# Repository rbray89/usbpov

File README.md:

# usbpov

A small USB configurable POV toy

Some portions of this project are under the GNU General Public License (USB Device Driver Code for Atmel Devices) and should be distributed as-such. The licensing information can be found in /usbPOV-src/usbdrv

The remainder of the project is under the following license:

The MIT License (MIT)

Copyright (c) 2013-2014 Ryan Bray

Permission is hereby granted, free of charge, to any person obtaining a copy of this software and associated documentation files (the "Software"), to deal in the Software without restriction, including without limitation the rights to use, copy, modify, merge, publish, distribute, sublicense, and/or sell copies of the Software, and to permit persons to whom the Software is furnished to do so, subject to the following conditions:

The above copyright notice and this permission notice shall be included in all copies or substantial portions of the Software.

THE SOFTWARE IS PROVIDED "AS IS", WITHOUT WARRANTY OF ANY KIND, EXPRESS OR IMPLIED, INCLUDING BUT NOT LIMITED TO THE WARRANTIES OF MERCHANTABILITY, FITNESS FOR A PARTICULAR PURPOSE AND NONINFRINGEMENT. IN NO EVENT SHALL THE AUTHORS OR COPYRIGHT HOLDERS BE LIABLE FOR ANY CLAIM, DAMAGES OR OTHER LIABILITY, WHETHER IN AN ACTION OF CONTRACT, TORT OR OTHERWISE, ARISING FROM, OUT OF OR IN CONNECTION WITH THE SOFTWARE OR THE USE OR OTHER DEALINGS IN THE SOFTWARE.

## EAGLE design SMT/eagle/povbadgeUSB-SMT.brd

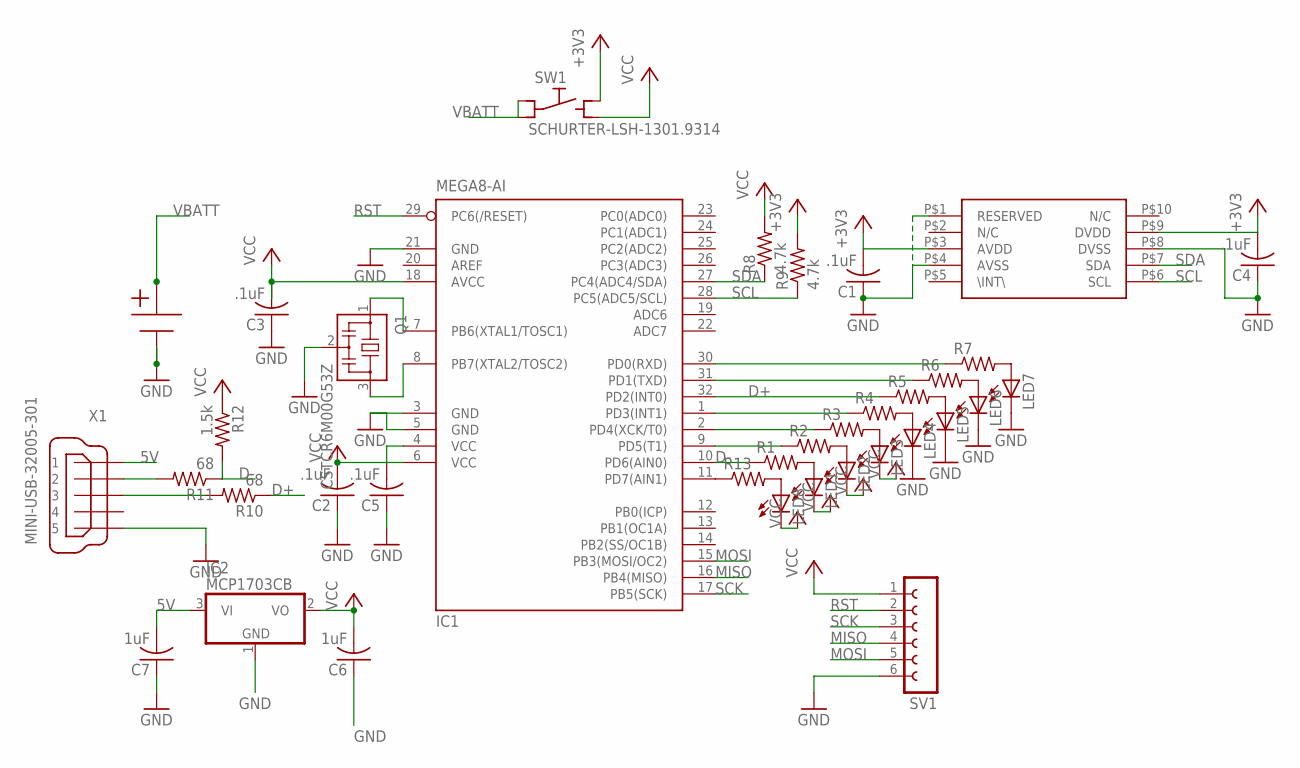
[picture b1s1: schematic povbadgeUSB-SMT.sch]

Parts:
C1, C2, C3, C4, C5: .1uF; C0805
C6, C7: 1uF; C0805
IC1: MEGA8-AI; TQFP32-08
IC2: MCP1703CB; SOT23
LED1, LED2, LED3, LED4, LED5, LED6, LED7, LED8: LEDCHIPLED_0805; CHIPLED_0805
MMA7660: MMA7660; DFN-10-HAND
Q1: CSTCR6M00G53Z; CSTCR6M
R1, R2, R3, R4, R5, R6, R7, R13: R-US_R0805; R0805
R8, R9: 4.7k; R0805
R10, R11: 68; R0805
R12: 1.5k; R0805
SV1: FE06W
SW1: SCHURTER-LSH-1301.9314; LSH
U$1: CR2032-CLIP; CR2032
X1: MINI-USB-32005-301; 32005-301

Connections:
5V: C7.2, IC2.3 (VI), X1.1
+3V3: C1.2, C4.2, MMA7660.P$3 (AVDD), MMA7660.P$9 (DVDD), R9.2, SW1.NO1 (NO)
D+: IC1.32 (PD2(INT0)), R5.1, R10.1
D-: IC1.10 (PD6(AIN0)), R1.1, R11.1, R12.2
GND: C1.1, C2.1, C3.1, C4.1, C5.1, C6.1, C7.1, IC1.3 (GND), IC1.5 (GND), IC1.21 (GND), IC2.1 (GND), LED4.C, LED5.C, LED6.C, LED7.C, MMA7660.P$1 (RESERVED), MMA7660.P$4 (AVSS), MMA7660.P$8 (DVSS), Q1.2, SV1.6, U$1.P$3, X1.5
INT1: IC1.1 (PD3(INT1)), R4.1
MISO: IC1.16 (PB4(MISO)), SV1.4
MOSI: IC1.15 (PB3(MOSI/OC2)), SV1.5
unnamed: LED1.A, R1.2
unnamed: IC1.11 (PD7(AIN1)), R13.1
unnamed: IC1.8 (PB7(XTAL2/TOSC2)), Q1.3
unnamed: IC1.7 (PB6(XTAL1/TOSC1)), Q1.1
unnamed: IC1.9 (PD5(T1)), R2.1
unnamed: LED8.A, R13.2
unnamed: LED2.A, R2.2
unnamed: LED3.A, R3.2
unnamed: LED4.A, R4.2
unnamed: LED5.A, R5.2
unnamed: LED6.A, R6.2
unnamed: LED7.A, R7.2
unnamed: R11.2, X1.2
unnamed: R10.2, X1.3
RST: IC1.29 (PC6(/RESET)), SV1.2
RXD: IC1.30 (PD0(RXD)), R7.1
SCK: IC1.17 (PB5(SCK)), SV1.3
SCL: IC1.28 (PC5(ADC5/SCL)), MMA7660.P$6 (SCL), R9.1
SDA: IC1.27 (PC4(ADC4/SDA)), MMA7660.P$7 (SDA), R8.1
TXD: IC1.31 (PD1(TXD)), R6.1
VBATT: SW1.C1 (C), SW1.C2 (C), U$1.P$1
VCC: C2.2, C3.2, C5.2, C6.2, IC1.4 (VCC), IC1.6 (VCC), IC1.18 (AVCC), IC2.2 (VO), LED1.C, LED2.C, LED3.C, LED8.C, R8.2, R12.1, SV1.1, SW1.NO2 (NO)
XCK: IC1.2 (PD4(XCK/T0)), R3.1

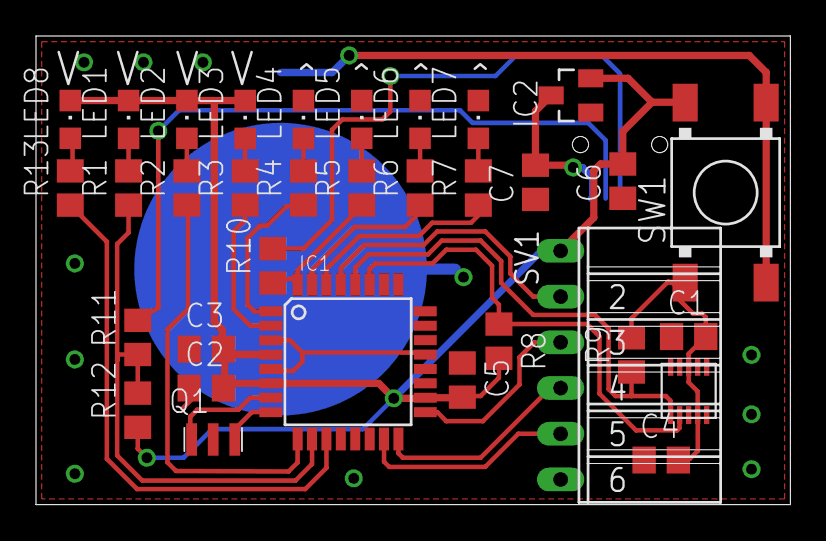
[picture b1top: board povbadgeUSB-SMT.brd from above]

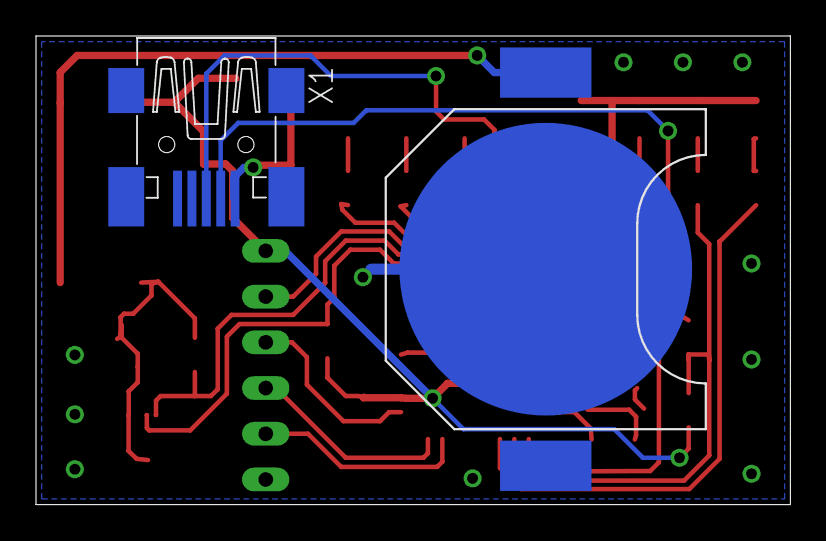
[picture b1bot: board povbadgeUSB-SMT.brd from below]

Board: 2 copper layers, 41.9 x 26.0 mm, 36 parts (2 on the bottom side), 31 nets.

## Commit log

2014-04-05 Init Commit
2014-04-05 added schematics info
